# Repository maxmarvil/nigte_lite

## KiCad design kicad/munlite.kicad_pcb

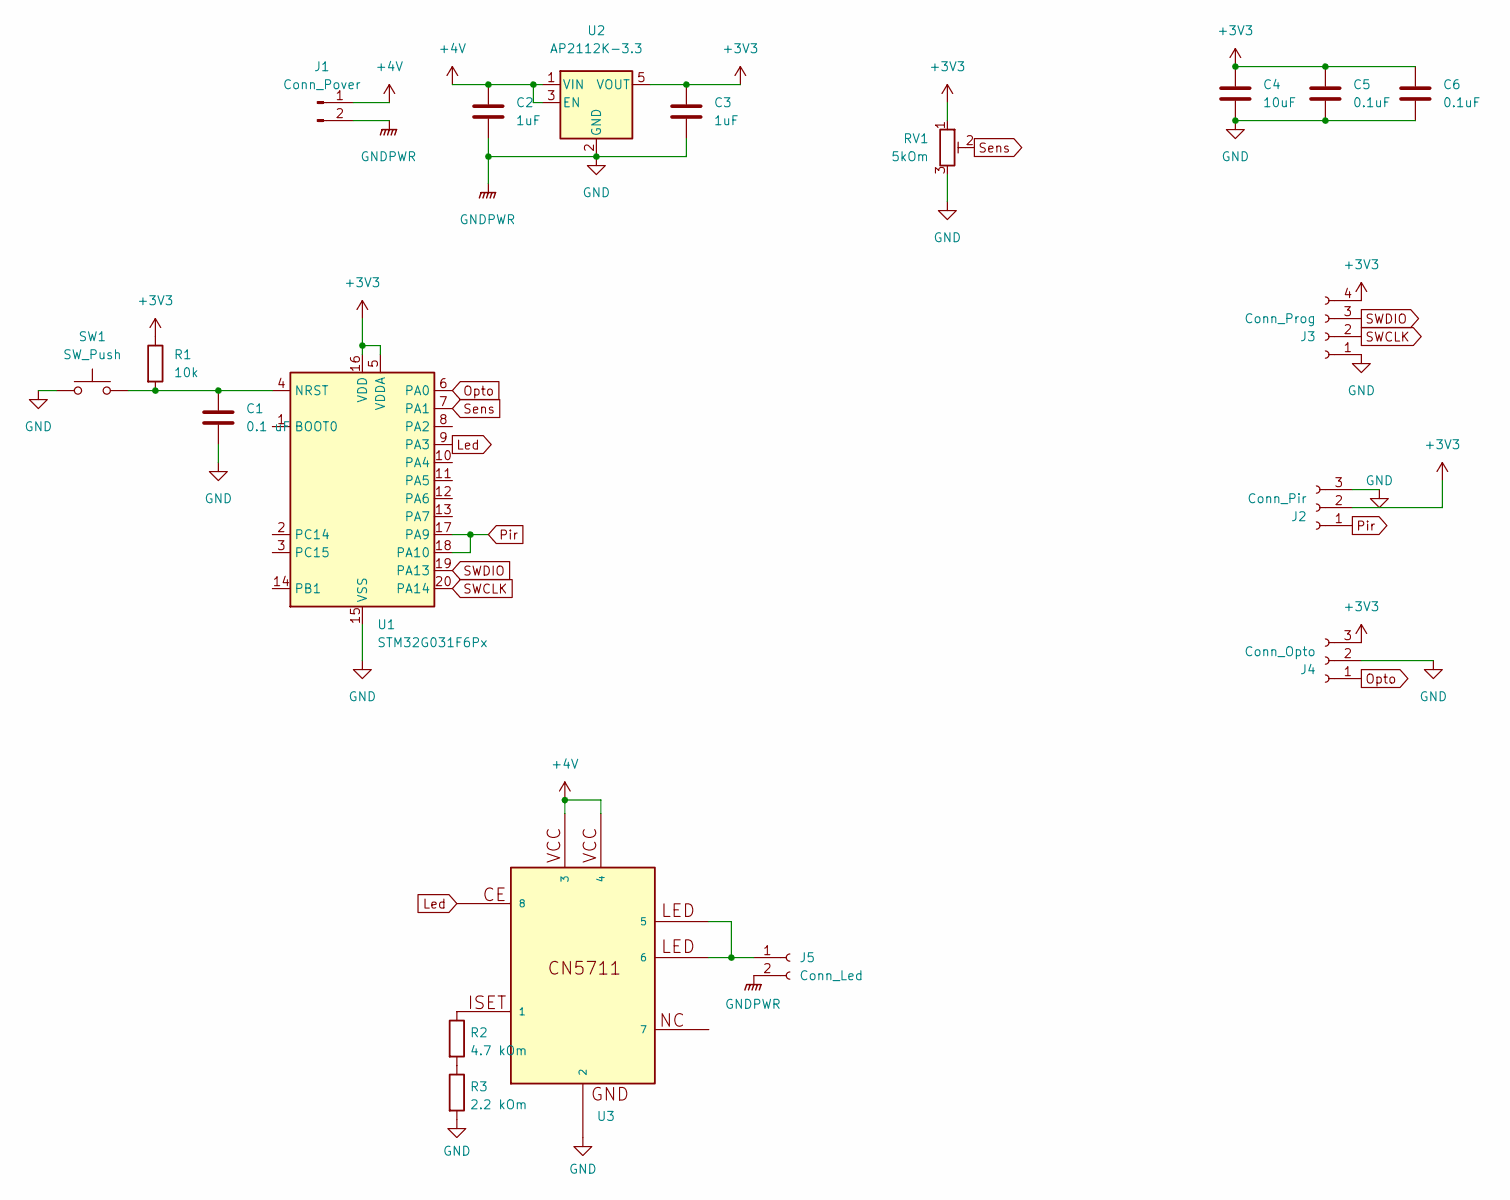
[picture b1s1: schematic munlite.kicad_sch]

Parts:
C1: 0.1 uF; C_1206_3216Metric
C2, C3: 1uF; C_1206_3216Metric
C4: 10uF; C_1206_3216Metric
C5, C6: 0.1uF; C_1206_3216Metric
J1: Conn_Pover; JST_XH_B2B-XH-AM_1x02_P2.50mm_Vertical
J2: Conn_Pir; PinSocket_1x03_P2.54mm_Vertical
J3: Conn_Prog; PinSocket_1x04_P2.54mm_Vertical
J4: Conn_Opto; PinSocket_1x03_P2.54mm_Vertical
J5: Conn_Led; JST_XA_B02B-XASK-1_1x02_P2.50mm_Vertical
R1: 10k; R_1206_3216Metric
R2: 4.7 kOm; R_1206_3216Metric
R3: 2.2 kOm; R_1206_3216Metric
RV1: 5kOm; Potentiometer_Bourns_TC33X_Vertical
SW1: SW_Push; SW_Push_SPST_NO_Alps_SKRK
U1: STM32G031F6Px; TSSOP-20_4.4x6.5mm_P0.65mm
U2: AP2112K-3.3; SOT-23-5
U3: CN5711; SOIC-8-1EP_3.9x4.9mm_P1.27mm_EP2.29x3mm

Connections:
+3V3: C3.1, C4.1, C5.1, C6.1, J2.2, J3.4, J4.3, R1.1, RV1.1, U1.5 (VDDA), U1.16 (VDD), U2.5 (VOUT)
+4V: C2.1, J1.1, U2.1 (VIN), U2.3 (EN), U3.3, U3.4
GND: C1.2, C2.2, C3.2, C4.2, C5.2, C6.2, J1.2, J2.3, J3.1, J4.2, J5.2, R3.2, RV1.3, SW1.1, U1.15 (VSS), U2.2 (GND), U3.2
Led: U1.9 (PA3), U3.8
unnamed: J5.1, U3.5, U3.6
unnamed: R2.1, U3.1
unnamed: R2.2, R3.1
unnamed: C1.1, R1.2, SW1.2, U1.4 (NRST)
Opto: J4.1, U1.6 (PA0)
Pir: J2.1, U1.17 (PA9), U1.18 (PA10)
SWCLK: J3.2, U1.20 (PA14)
SWDIO: J3.3, U1.19 (PA13)
Sens: RV1.2, U1.7 (PA1)

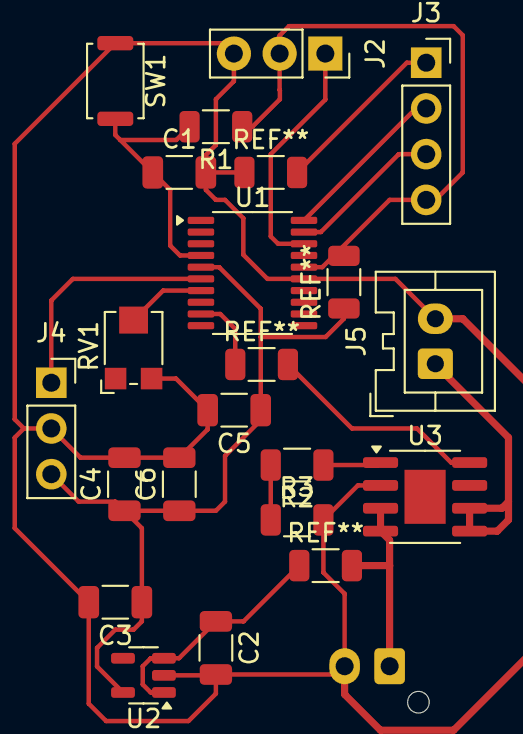
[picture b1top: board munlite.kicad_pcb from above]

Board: 2 copper layers, 19 parts (1 on the bottom side), 13 nets.

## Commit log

2022-06-05 init
2022-06-05 update fade
2022-06-08 gitignore update
2022-06-10 update gitignore
2022-06-10 set timer simple
2022-06-11 pir + timer stable
2022-06-12 clear readme
2022-06-13 opto condition
2022-06-13 no pwm
2022-06-13 clock update
2022-06-14 pwm enable
2022-06-14 opto data, hal from github
2022-06-19 tasks
2022-06-19 tasks up
2022-06-19 tasks wip
2022-06-19 fix panic
2022-06-26 option-handler
2022-06-26 fix status stick
2022-06-28 deep sleep
2022-06-30 clear
2022-07-04 +rtt, not work
2022-07-10 wip , add mutex, and interrupt
2022-07-10 to branch, no sleep
2022-07-10 interrup pir
2022-07-12 interrup update
2022-07-12 interrup wip
2022-07-15 add pwm
2022-07-17 wip +pwm + configuration optotransistor
2022-07-17 sleeping
2022-07-20 kicad
2022-07-28 kicad update
2022-08-09 kicad: update pcb
2022-08-10 wip 3d
2022-08-28 to update
2022-08-30 update pcb
2022-09-02 update board
2022-09-04 debug wip
2022-09-19 add kikad base
2024-12-15 iml file
2025-01-19 to embassy
2025-08-10 update rust, deprecated
2025-08-20 see branches
